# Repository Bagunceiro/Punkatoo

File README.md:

# Punkatoo

Fan and Lamp messages -> JSON
IR Reset code (c. light up)
MQTTController::publish - why is the delay needed

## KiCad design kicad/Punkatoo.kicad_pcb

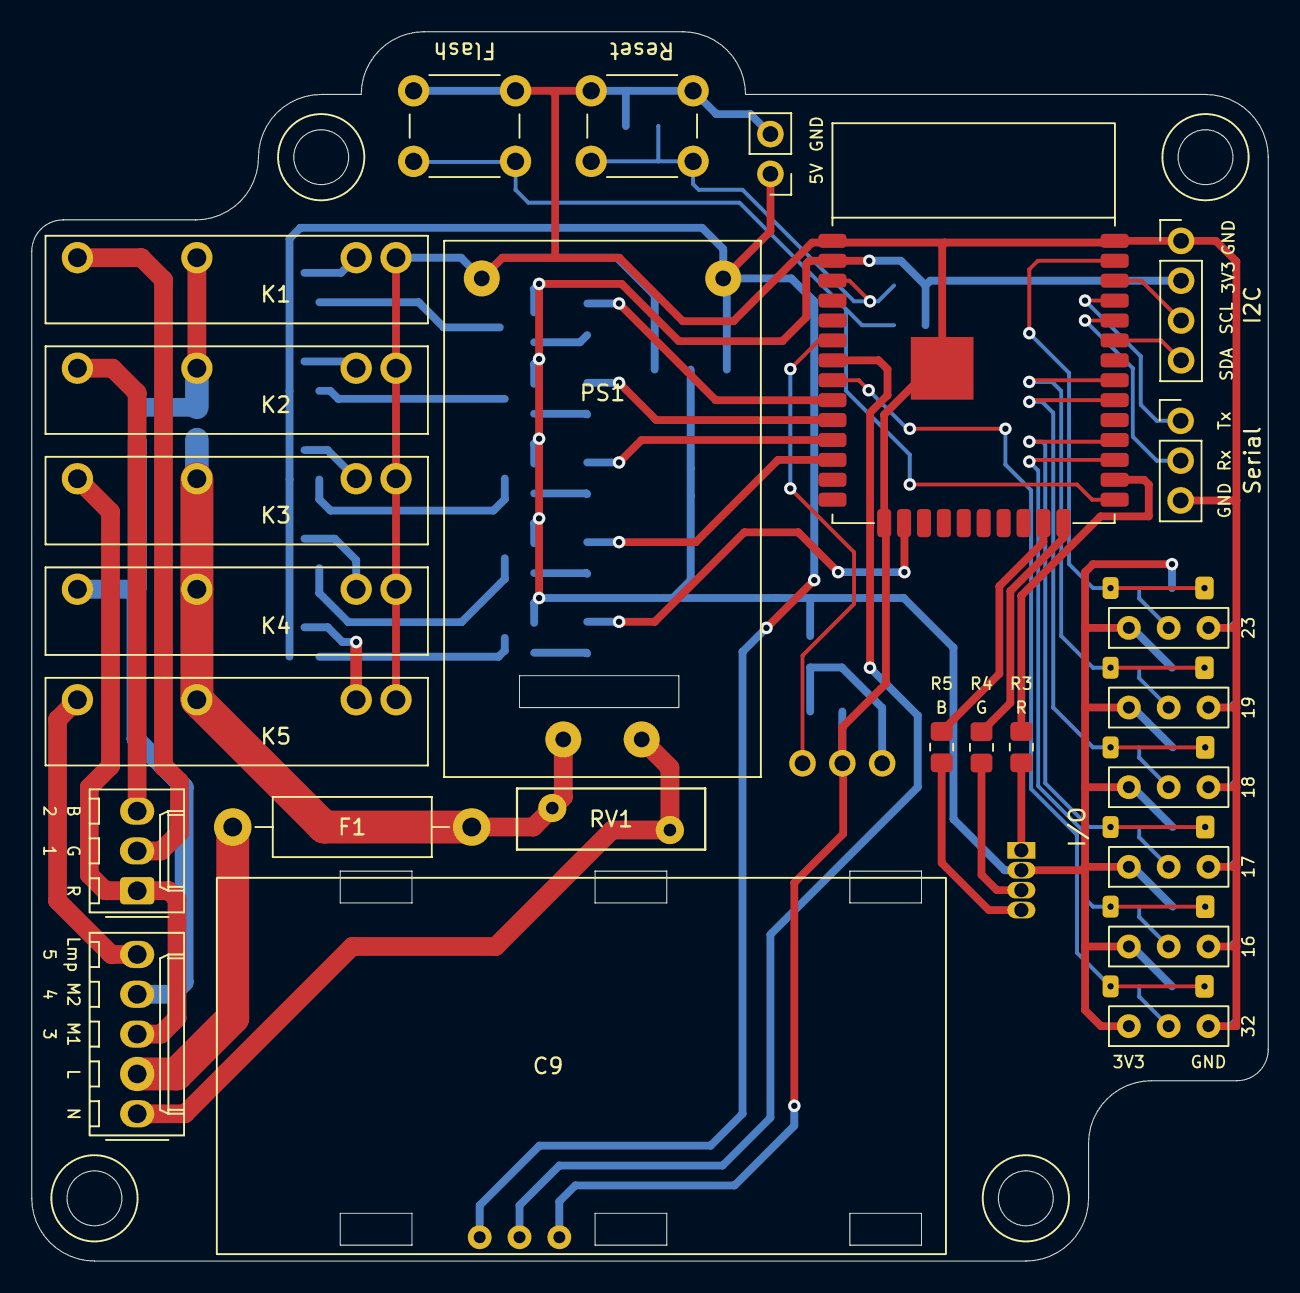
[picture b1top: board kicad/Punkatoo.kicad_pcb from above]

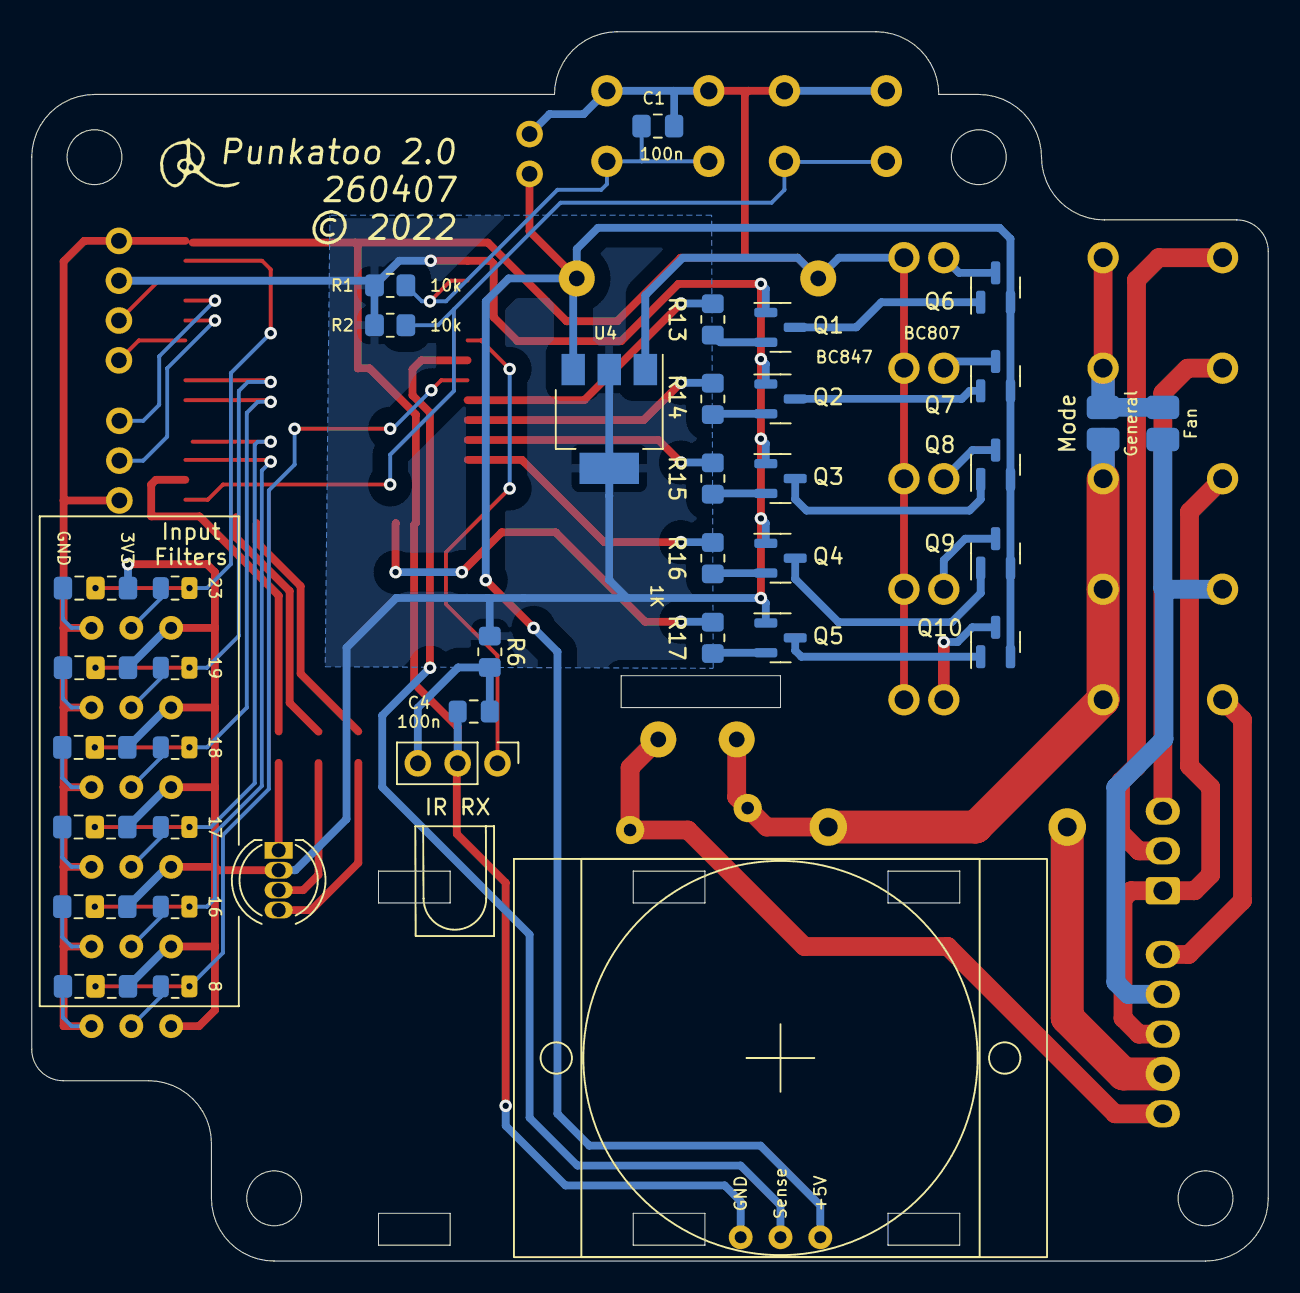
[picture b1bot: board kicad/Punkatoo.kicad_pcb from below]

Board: 2 copper layers, 78.9 x 78.4 mm, 59 parts (38 on the bottom side), 59 nets.

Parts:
C1: 100n; C_0805_2012Metric_Pad1.18x1.45mm_HandSolder
C2, C3, C5, C6, C7, C8: C_Option; C_0805_Option
C4: 100n; C_0805_2012Metric_Pad1.15x1.40mm_HandSolder
C9: Capacitor; 3Wire_2.5uF+4.5uF
D1: LED_RGBA; LED_D5.0mm-4_RGB
F1: 3A; R_Axial_DIN0411_L9.9mm_D3.6mm_P15.24mm_Horizontal
J1: 5V Power; PinHeader_1x02_P2.54mm_Vertical
J2: Serial; PinHeader_1x03_P2.54mm_Vertical
J3: I/O; Conn_03x06
J4: I2C; PinHeader_1x04_P2.54mm_Vertical
J5: Capacitor; Molex_KK-254_AE-6410-03A_1x03_P2.54mm_Vertical
J6: A/C; Molex_KK-254_AE-6410-05A_1x05_P2.54mm_Vertical
JP1: General; R_0805_2012Metric_Pad1.15x1.40mm_HandSolder
JP2: Fan; R_0805_2012Metric_Pad1.15x1.40mm_HandSolder
K1, K2, K3, K4, K5: G3MB-Relay_SolidState; G3MB
PS1: HLK-PM01; HLK-PMxx
Q1, Q2, Q3, Q4, Q5: BC847; SOT-23
Q6, Q7, Q8, Q9, Q10: BC807; SOT-23
R1, R2: 10k; R_0805_2012Metric_Pad1.20x1.40mm_HandSolder
R3: R; R_0805_2012Metric_Pad1.20x1.40mm_HandSolder
R4: G; R_0805_2012Metric_Pad1.20x1.40mm_HandSolder
R5: B; R_0805_2012Metric_Pad1.20x1.40mm_HandSolder
R6: 100; R_0805_2012Metric_Pad1.20x1.40mm_HandSolder
R7, R8, R9, R10, R11, R12: 1K; R_0805+THT
R13, R14, R15, R16, R17: 1K; R_0805_2012Metric_Pad1.20x1.40mm_HandSolder
RV1: Varistor; RV_Disc_D12mm_W3.9mm_P7.5mm
SW1: Reset; SW_PUSH_6mm_H5mm
SW2: Flash; SW_PUSH_6mm_H5mm
U1: ESP32-WROOM-32; wroom32
U2: PIR
U3: IR RX; TSOP38
U4: AMS1117-3.3; SOT-223-3_TabPin2

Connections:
+3V3: C2.1, C3.1, C5.1, C6.1, C7.1, C8.1, D1.2 (A), J3.7, J4.2, Q1.1 (B), Q2.1 (B), Q3.1 (B), Q4.1 (B), Q5.1 (B), R1.2, R2.1, R6.1, U1.2 (VDD), U4.2 (VO)
+5V: J1.1, PS1.4 (+Vout), Q6.2 (E), Q7.2 (E), Q8.2 (E), Q9.2 (E), Q10.2 (E), U2.3 (V+), U4.3 (VI)
/8: C2.2, R7.1, U1.8 (IO32)
/16: C3.2, R8.1, U1.27 (IO16)
/17: C5.2, R9.1, U1.28 (IO17)
/18: C6.2, R10.1, U1.30 (IO18)
/19: C7.2, R11.1, U1.31 (IO19)
/23: C8.2, R12.1, U1.37 (IO23)
/C_Blue: J5.3, K2.1
/C_Green: J5.2, K1.1
/C_Red: J5.1, J6.3, K3.1
/Flash: R2.2, SW2.1, U1.25 (IO0)
/IR: U1.6 (IO34), U3.1 (OUT)
/IndB: R5.1, U1.23 (IO15)
/IndG: R4.1, U1.24 (IO2)
/IndR: R3.1, U1.26 (IO4)
/LINE: F1.2, J6.2
/LMP: J6.5, K5.1
/M2: J6.4, JP2.2 (B), K4.1
/PIR: U1.7 (IO35), U2.2 (OUT)
/RXD: J2.2, U1.34 (RXD0/IO3)
/Reset: C1.2, R1.1, SW1.2, U1.3 (EN)
/TXD: J2.1, U1.35 (TXD0/IO1)
Fused: F1.1, JP1.2 (B), K3.2, K4.2, K5.2, PS1.1 (AC/L), RV1.2
GND: C1.1, C2.3, C3.3, C4.2, C5.3, C6.3, C7.3, C8.3, J1.2, J2.3, J3.8, J4.1, K1.4 (INP-), K2.4 (INP-), K3.4 (INP-), K4.4 (INP-), K5.4 (INP-), PS1.3 (-Vout), SW1.1, SW2.2, U1.1 (GND), U1.15 (GND), U1.38 (GND), U1.39 (GND), U2.1 (GND), U3.2 (GND), U4.1 (GND)
unnamed: C4.1, R6.2, U3.3 (Vs)
unnamed: D1.1 (RK), R3.2
unnamed: D1.3 (GK), R4.2
unnamed: D1.4 (BK), R5.2
unnamed: J3.1, R12.2
unnamed: J3.2, R11.2
unnamed: J3.3, R10.2
unnamed: J3.4, R9.2
unnamed: J3.5, R8.2
unnamed: J3.6, R7.2
unnamed: J4.3, U1.36 (IO22)
unnamed: J4.4, U1.33 (IO21)
unnamed: JP1.1 (A), JP2.1 (A), K1.2, K2.2
unnamed: K1.3 (INP+), Q6.3 (C)
unnamed: K2.3 (INP+), Q7.3 (C)
unnamed: K3.3 (INP+), Q8.3 (C)
unnamed: K4.3 (INP+), Q9.3 (C)
unnamed: K5.3 (INP+), Q10.3 (C)
unnamed: Q1.2 (E), R13.2
unnamed: Q1.3 (C), Q6.1 (B)
unnamed: Q2.2 (E), R14.2
unnamed: Q2.3 (C), Q7.1 (B)
unnamed: Q3.2 (E), R15.2
unnamed: Q3.3 (C), Q8.1 (B)
unnamed: Q4.2 (E), R16.2
unnamed: Q4.3 (C), Q9.1 (B)
unnamed: Q5.2 (E), R17.1
unnamed: Q5.3 (C), Q10.1 (B)
Neutral: J6.1, PS1.2 (AC/N), RV1.1
R1: R13.1, U1.9 (IO33)
R2: R14.1, U1.10 (IO25)
R3: R15.1, U1.11 (IO26)
R4: R16.1, U1.12 (IO27)
R5: R17.2, U1.16 (IO13)

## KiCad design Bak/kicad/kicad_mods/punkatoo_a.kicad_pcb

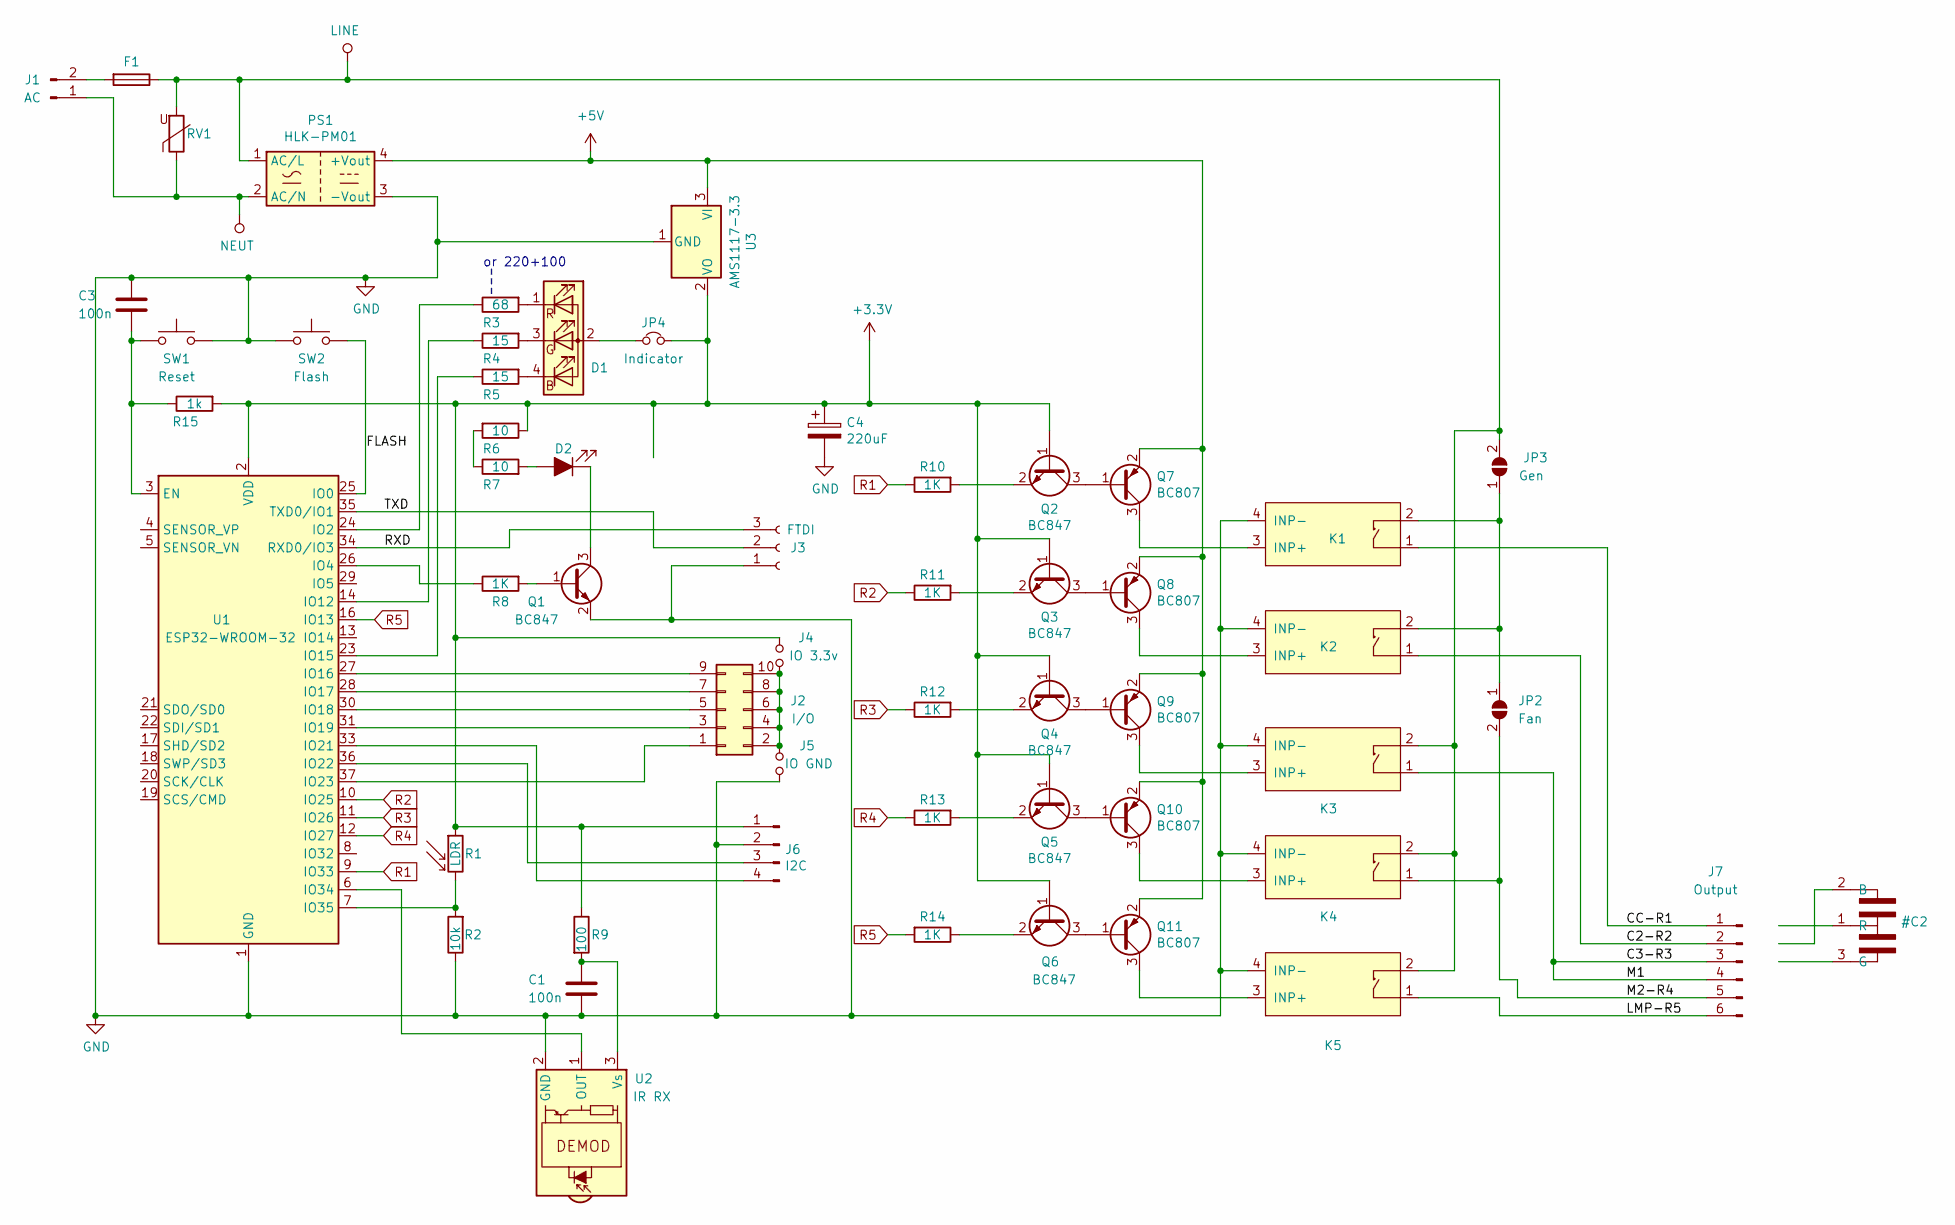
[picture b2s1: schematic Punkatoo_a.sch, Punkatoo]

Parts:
C1, C3: 100n; C_0805_2012Metric_Pad1.15x1.40mm_HandSolder
C4: 220uF; CP_Radial_D8.0mm_P2.50mm
D1: LED_RGBA; LED_D5.0mm-4_RGB
D2: IR TX; LED_D5.0mm
F1: Fuse; R_Axial_DIN0411_L9.9mm_D3.6mm_P15.24mm_Horizontal
J1: AC; Molex_KK-254_AE-6410-02A_1x02_P2.54mm_Vertical
J2: I/O; PinHeader_2x05_P2.54mm_Vertical
J3: FTDI; PinSocket_1x03_P2.54mm_Vertical
J4: IO 3.3v; R_0805_2012Metric_Pad1.15x1.40mm_HandSolder
J5: IO GND; R_0805_2012Metric_Pad1.15x1.40mm_HandSolder
J6: I2C; PinHeader_1x04_P2.54mm_Vertical
J7: Output; Molex_KK-254_AE-6410-06A_1x06_P2.54mm_Vertical
JP2: Fan; R_0805_2012Metric_Pad1.15x1.40mm_HandSolder
JP3: Gen; R_0805_2012Metric_Pad1.15x1.40mm_HandSolder
JP4: Indicator; PinHeader_1x02_P2.54mm_Vertical
K1, K2, K3, K4: G3MB
K5: G3MB-Relay_SolidState; G3MB
PS1: HLK-PM01; Converter_ACDC_HiLink_HLK-PMxx
Q1, Q2, Q3, Q4, Q5, Q6: BC847; SOT-23_HandSoldering
Q7, Q8, Q9, Q10, Q11: BC807; SOT-23_HandSoldering
R1: LDR; R_LDR_5.1x4.3mm_P3.4mm_Vertical
R2: 10k; R_0805_2012Metric_Pad1.15x1.40mm_HandSolder
R3: 68; R_0805_2012Metric_Pad1.15x1.40mm_HandSolder
R4, R5: 15; R_0805_2012Metric_Pad1.15x1.40mm_HandSolder
R6, R7: 10; R_0805_2012Metric_Pad1.15x1.40mm_HandSolder
R8, R10, R11, R12, R13, R14: 1K; R_0805_2012Metric_Pad1.15x1.40mm_HandSolder
R9: 100; R_0805_2012Metric_Pad1.15x1.40mm_HandSolder
R15: 1k; R_0805_2012Metric_Pad1.15x1.40mm_HandSolder
RV1: Varistor; varistor_10mm
SW1: Reset; SW_Tactile_Straight_KSL0Axx1LFTR
SW2: Flash; SW_Tactile_Straight_KSL0Axx1LFTR
U1: ESP32-WROOM-32
U2: IR RX; TSOP38
U3: AMS1117-3.3; SOT-223-3_TabPin2

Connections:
+3V3: C4.1, J4.1, J6.1, JP4.1, Q2.1 (B), Q3.1 (B), Q4.1 (B), Q5.1 (B), Q6.1 (B), R1.1, R6.1, R9.1, R15.2, U1.2 (VDD), U3.2 (VO)
+5V: PS1.4 (+Vout), Q7.2 (E), Q8.2 (E), Q9.2 (E), Q10.2 (E), Q11.2 (E), U3.3 (VI)
/C2-R2: J7.2, K2.1
/C3-R3: J7.3, J7.4, K3.1
/CC-R1: J7.1, K1.1
/FLASH: SW2.1, U1.25 (IO0)
/LMP-R5: J7.6, K5.1
/M2-R4: J7.5, JP2.2 (B), K4.1
/RXD: J3.3, U1.34 (RXD0/IO3)
/TXD: J3.2, U1.35 (TXD0/IO1)
GND: C1.2, C3.1, C4.2, J3.1, J5.1, J6.2, K1.4 (INP-), K2.4 (INP-), K3.4 (INP-), K4.4 (INP-), K5.4 (INP-), PS1.3 (-Vout), Q1.2 (E), R2.1, SW1.1, SW2.2, U1.1 (GND), U1.15 (GND), U1.38 (GND), U1.39 (GND), U2.2 (GND), U3.1 (GND)
LINE: F1.1, JP3.2 (B), K3.2, K4.2, K5.2, PS1.1 (AC/L), RV1.2
NEUT: J1.1, PS1.2 (AC/N), RV1.1
unnamed: C1.1, R9.2, U2.3 (Vs)
unnamed: C3.2, R15.1, SW1.2, U1.3 (EN)
unnamed: D1.1 (RK), R3.2
unnamed: D1.2 (A), JP4.2
unnamed: D1.3 (GK), R4.2
unnamed: D1.4 (BK), R5.2
unnamed: D2.1 (K), Q1.3 (C)
unnamed: D2.2 (A), R7.2
unnamed: F1.2, J1.2
unnamed: J2.1, U1.37 (IO23)
unnamed: J2.3, U1.31 (IO19)
unnamed: J2.5, U1.30 (IO18)
unnamed: J2.7, U1.28 (IO17)
unnamed: J2.9, U1.27 (IO16)
unnamed: J2.2, J2.4, J2.6, J2.8, J2.10, J4.2, J5.2
unnamed: J6.3, U1.36 (IO22)
unnamed: J6.4, U1.33 (IO21)
unnamed: JP2.1 (A), JP3.1 (A), K1.2, K2.2
unnamed: K1.3 (INP+), Q7.3 (C)
unnamed: K2.3 (INP+), Q8.3 (C)
unnamed: K3.3 (INP+), Q9.3 (C)
unnamed: K4.3 (INP+), Q10.3 (C)
unnamed: K5.3 (INP+), Q11.3 (C)
unnamed: Q1.1 (B), R8.2
unnamed: Q2.2 (E), R10.2
unnamed: Q2.3 (C), Q7.1 (B)
unnamed: Q3.2 (E), R11.2
unnamed: Q3.3 (C), Q8.1 (B)
unnamed: Q4.2 (E), R12.2
unnamed: Q4.3 (C), Q9.1 (B)
unnamed: Q5.2 (E), R13.2
unnamed: Q6.2 (E), R14.1
unnamed: Q5.3 (C), Q10.1 (B)
unnamed: Q6.3 (C), Q11.1 (B)
unnamed: R1.2, R2.2, U1.7 (IO35)
unnamed: R3.1, U1.24 (IO2)
unnamed: R4.1, U1.14 (IO12)
unnamed: R5.1, U1.23 (IO15)
unnamed: R6.2, R7.1
unnamed: R8.1, U1.26 (IO4)
unnamed: U1.6 (IO34), U2.1 (OUT)
R1: R10.1, U1.9 (IO33)
R2: R11.1, U1.10 (IO25)
R3: R12.1, U1.11 (IO26)
R4: R13.1, U1.12 (IO27)
R5: R14.2, U1.16 (IO13)

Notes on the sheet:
or 220+100

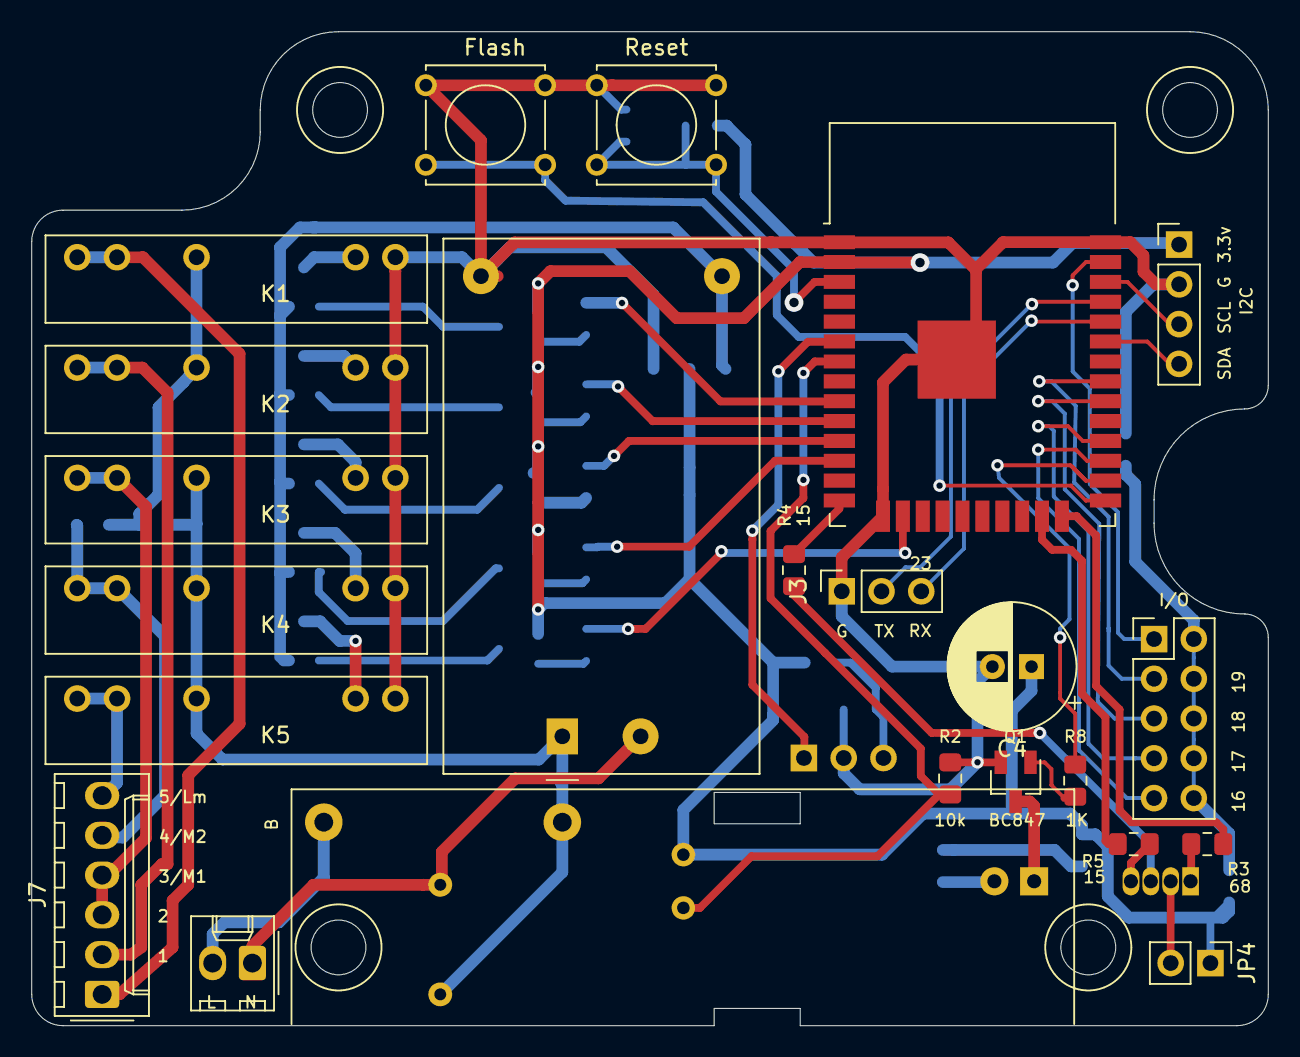
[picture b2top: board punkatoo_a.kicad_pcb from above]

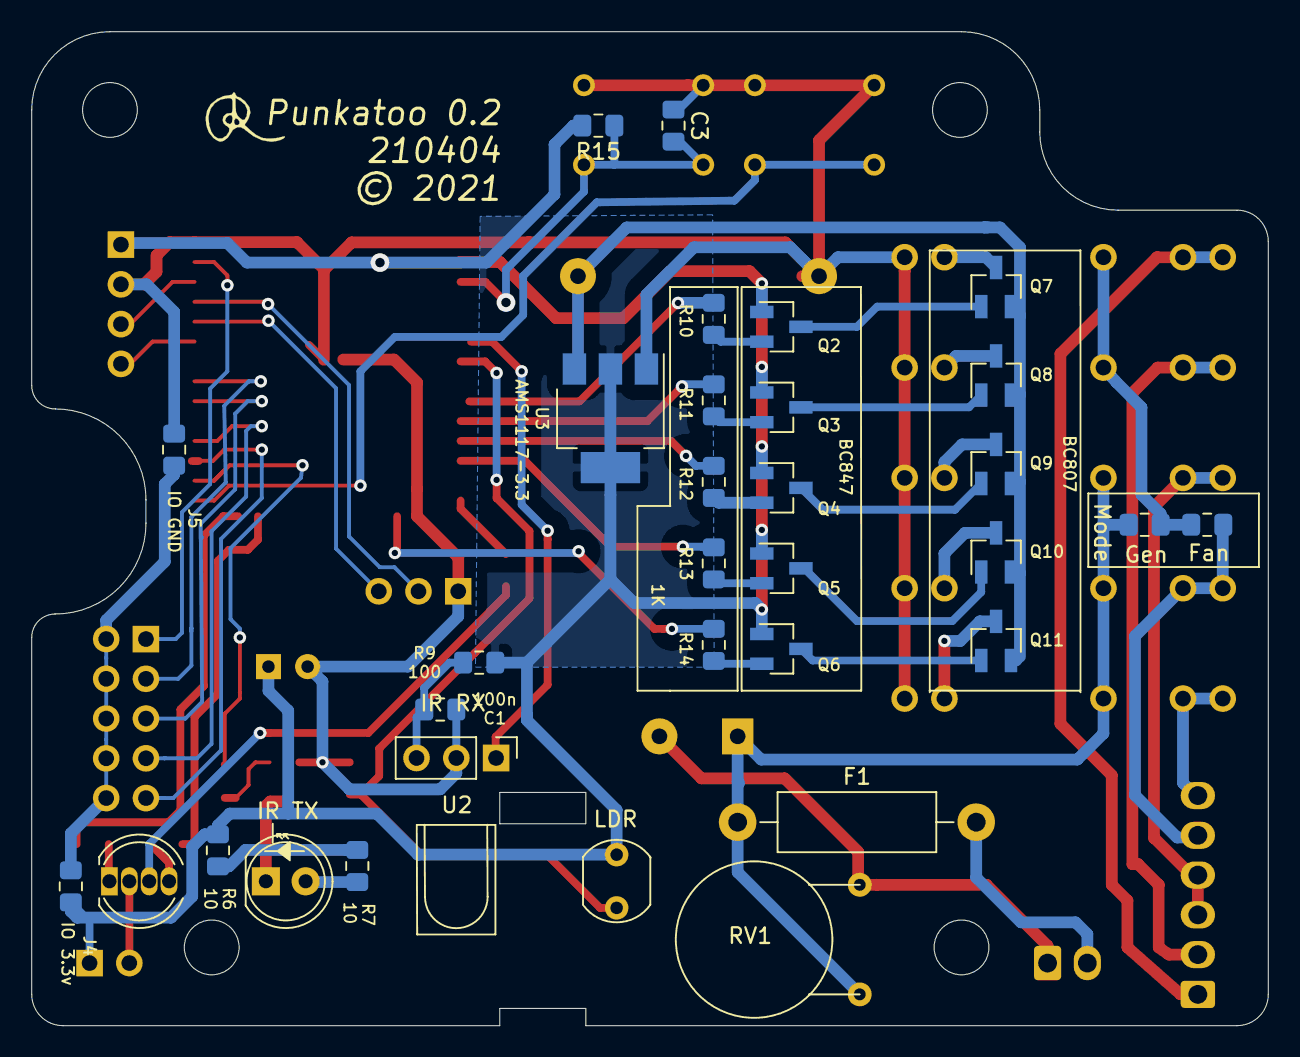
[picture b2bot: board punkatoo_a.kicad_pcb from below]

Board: 2 copper layers, 79.0 x 63.5 mm, 55 parts (32 on the bottom side), 59 nets.

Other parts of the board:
Capacitor: Ceiling_Fan_Capacitor

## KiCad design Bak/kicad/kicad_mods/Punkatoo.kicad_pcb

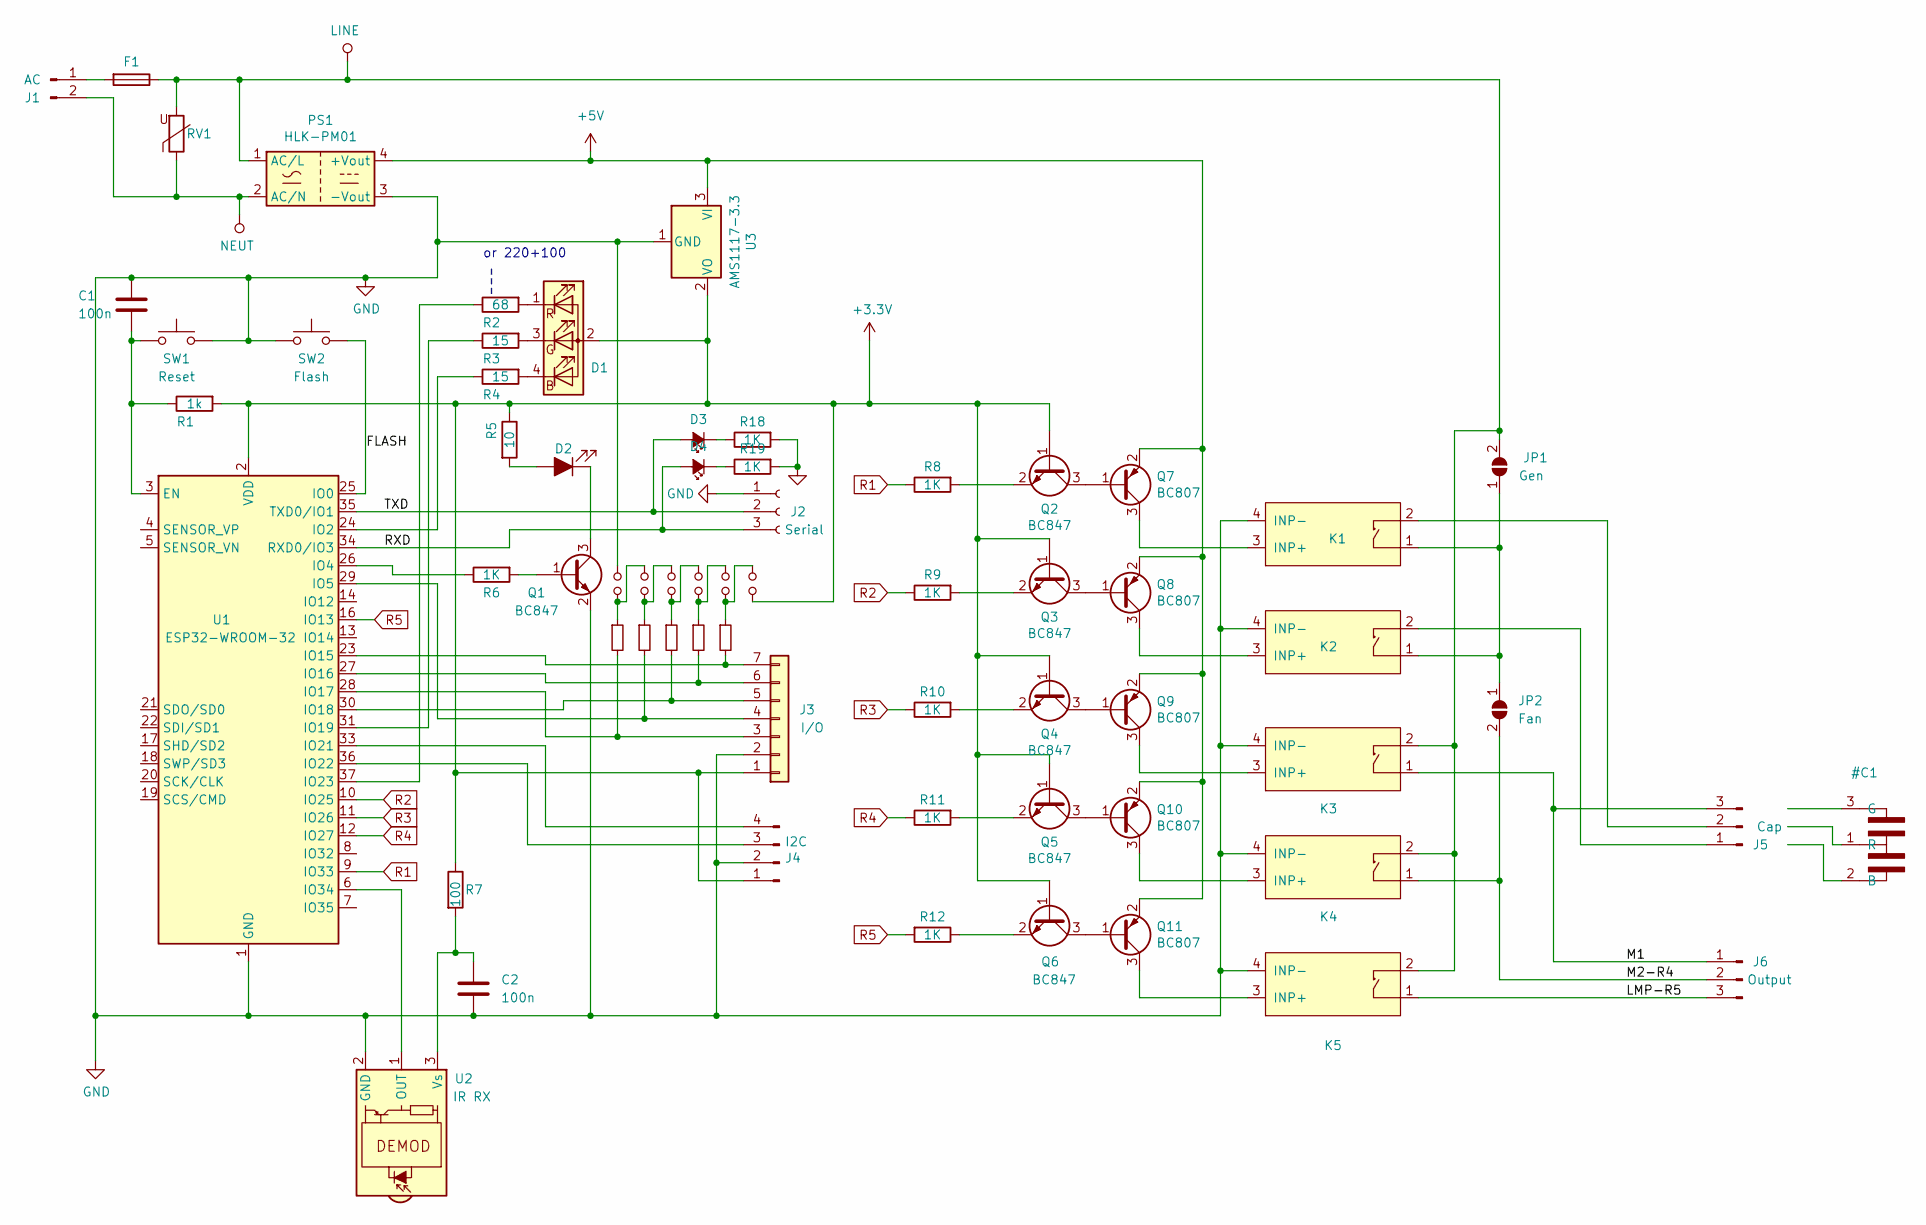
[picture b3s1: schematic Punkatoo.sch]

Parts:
C1, C2: 100n; C_0805_2012Metric_Pad1.15x1.40mm_HandSolder
D1: RGB; LED_D5.0mm-4_RGB
D2: IR TX; LED_D5.0mm
D3, D4: LED_Small_ALT; LED_0805_2012Metric_Pad1.15x1.40mm_HandSolder
F1: Fuse; R_Axial_DIN0411_L9.9mm_D3.6mm_P15.24mm_Horizontal
J1: AC; Molex_KK-254_AE-6410-02A_1x02_P2.54mm_Vertical
J2: Serial; PinHeader_1x03_P2.54mm_Vertical
J3: I/O; GPIO_5+rails_P2.54mm_Vertical
J4: I2C; PinHeader_1x04_P2.54mm_Vertical
J5: Cap; Molex_KK-254_AE-6410-03A_1x03_P2.54mm_Vertical
J6: Output; Molex_KK-254_AE-6410-03A_1x03_P2.54mm_Vertical
JP1: Gen; R_0805_2012Metric_Pad1.15x1.40mm_HandSolder
JP2: Fan; R_0805_2012Metric_Pad1.15x1.40mm_HandSolder
JP3: GND; Small_solder_jumper
JP4, JP5, JP6, JP7: Jumper_NO_Small; Small_solder_jumper
JP8: 3.3V; Small_solder_jumper
K1, K2, K3, K4: G3MB
K5: G3MB-Relay_SolidState; G3MB
PS1: HLK-PM01; Converter_ACDC_HiLink_HLK-PMxx
Q1, Q2, Q3, Q4, Q5, Q6: BC847; SOT-23_HandSoldering
Q7, Q8, Q9, Q10, Q11: BC807; SOT-23_HandSoldering
R1: 1k; R_0805_2012Metric_Pad1.15x1.40mm_HandSolder
R2: 68; R_0805_2012Metric_Pad1.15x1.40mm_HandSolder
R3, R4, R13: 15; R_0805_2012Metric_Pad1.15x1.40mm_HandSolder
R5: 10; R_0805_2012Metric_Pad1.15x1.40mm_HandSolder
R6, R8, R9, R10, R11, R12, R18, R19: 1K; R_0805_2012Metric_Pad1.15x1.40mm_HandSolder
R7: 100; R_0805_2012Metric_Pad1.15x1.40mm_HandSolder
R14: 16; R_0805_2012Metric_Pad1.15x1.40mm_HandSolder
R15: 18; R_0805_2012Metric_Pad1.15x1.40mm_HandSolder
R16: 5; R_0805_2012Metric_Pad1.15x1.40mm_HandSolder
R17: 17; R_0805_2012Metric_Pad1.15x1.40mm_HandSolder
RV1: Varistor; varistor_10mm
SW1: Reset; SW_Tactile_Straight_KSL0Axx1LFTR
SW2: Flash; SW_Tactile_Straight_KSL0Axx1LFTR
U1: ESP32-WROOM-32
U2: IR RX; TSOP38
U3: AMS1117-3.3; SOT-223-3_TabPin2

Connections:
+3V3: D1.2 (A), J3.1, J4.1, JP8.2, Q2.1 (B), Q3.1 (B), Q4.1 (B), Q5.1 (B), Q6.1 (B), R1.2, R5.1, R7.1, U1.2 (VDD), U3.2 (VO)
+5V: PS1.4 (+Vout), Q7.2 (E), Q8.2 (E), Q9.2 (E), Q10.2 (E), Q11.2 (E), U3.3 (VI)
/FLASH: SW2.1, U1.25 (IO0)
/LMP-R5: J6.3, K5.1
/M1: J5.3, J6.1, K3.1
/M2-R4: J6.2, JP2.2 (B), K4.1
/RXD: D4.2 (A), J2.3, U1.34 (RXD0/IO3)
/TXD: D3.2 (A), J2.2, U1.35 (TXD0/IO1)
GND: C1.1, C2.2, J2.1, J3.2, J4.2, JP3.1, K1.4 (INP-), K2.4 (INP-), K3.4 (INP-), K4.4 (INP-), K5.4 (INP-), PS1.3 (-Vout), Q1.2 (E), R18.2, R19.2, SW1.1, SW2.2, U1.1 (GND), U1.15 (GND), U1.38 (GND), U1.39 (GND), U2.2 (GND), U3.1 (GND); also elsewhere on the board
LINE: F1.1, JP1.2 (B), K3.2, K4.2, K5.2, PS1.1 (AC/L), RV1.2
NEUT: J1.2, PS1.2 (AC/N), RV1.1
unnamed: C1.2, R1.1, SW1.2, U1.3 (EN)
unnamed: C2.1, R7.2, U2.3 (Vs)
unnamed: D1.1 (RK), R2.2
unnamed: D1.3 (GK), R3.2
unnamed: D1.4 (BK), R4.2
unnamed: D2.1 (K), Q1.3 (C)
unnamed: D2.2 (A), R5.2
unnamed: D3.1 (K), R18.1
unnamed: D4.1 (K), R19.1
unnamed: F1.2, J1.1
unnamed: J3.3, R17.2, U1.28 (IO17)
unnamed: J3.4, R16.2, U1.29 (IO5)
unnamed: J3.5, R15.2, U1.30 (IO18)
unnamed: J3.6, R14.2, U1.27 (IO16)
unnamed: J3.7, R13.2, U1.23 (IO15)
unnamed: J4.3, U1.36 (IO22)
unnamed: J4.4, U1.33 (IO21)
unnamed: J5.1, K2.2
unnamed: J5.2, K1.2
unnamed: JP1.1 (A), JP2.1 (A), K1.1, K2.1
unnamed: JP3.2, JP4.1, R17.1
unnamed: JP4.2, JP5.1, R16.1
unnamed: JP5.2, JP6.1, R15.1
unnamed: JP6.2, JP7.1, R14.1
unnamed: JP7.2, JP8.1, R13.1
unnamed: K1.3 (INP+), Q7.3 (C)
unnamed: K2.3 (INP+), Q8.3 (C)
unnamed: K3.3 (INP+), Q9.3 (C)
unnamed: K4.3 (INP+), Q10.3 (C)
unnamed: K5.3 (INP+), Q11.3 (C)
unnamed: Q1.1 (B), R6.2
unnamed: Q2.2 (E), R8.2
unnamed: Q2.3 (C), Q7.1 (B)
unnamed: Q3.2 (E), R9.2
unnamed: Q3.3 (C), Q8.1 (B)
unnamed: Q4.2 (E), R10.2
unnamed: Q4.3 (C), Q9.1 (B)
unnamed: Q5.2 (E), R11.2
unnamed: Q6.2 (E), R12.1
unnamed: Q5.3 (C), Q10.1 (B)
unnamed: Q6.3 (C), Q11.1 (B)
unnamed: R2.1, U1.37 (IO23)
unnamed: R3.1, U1.31 (IO19)
unnamed: R4.1, U1.24 (IO2)
unnamed: R6.1, U1.26 (IO4)
unnamed: U1.6 (IO34), U2.1 (OUT)
R1: R8.1, U1.9 (IO33)
R2: R9.1, U1.10 (IO25)
R3: R10.1, U1.11 (IO26)
R4: R11.1, U1.12 (IO27)
R5: R12.2, U1.16 (IO13)

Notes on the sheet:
or 220+100

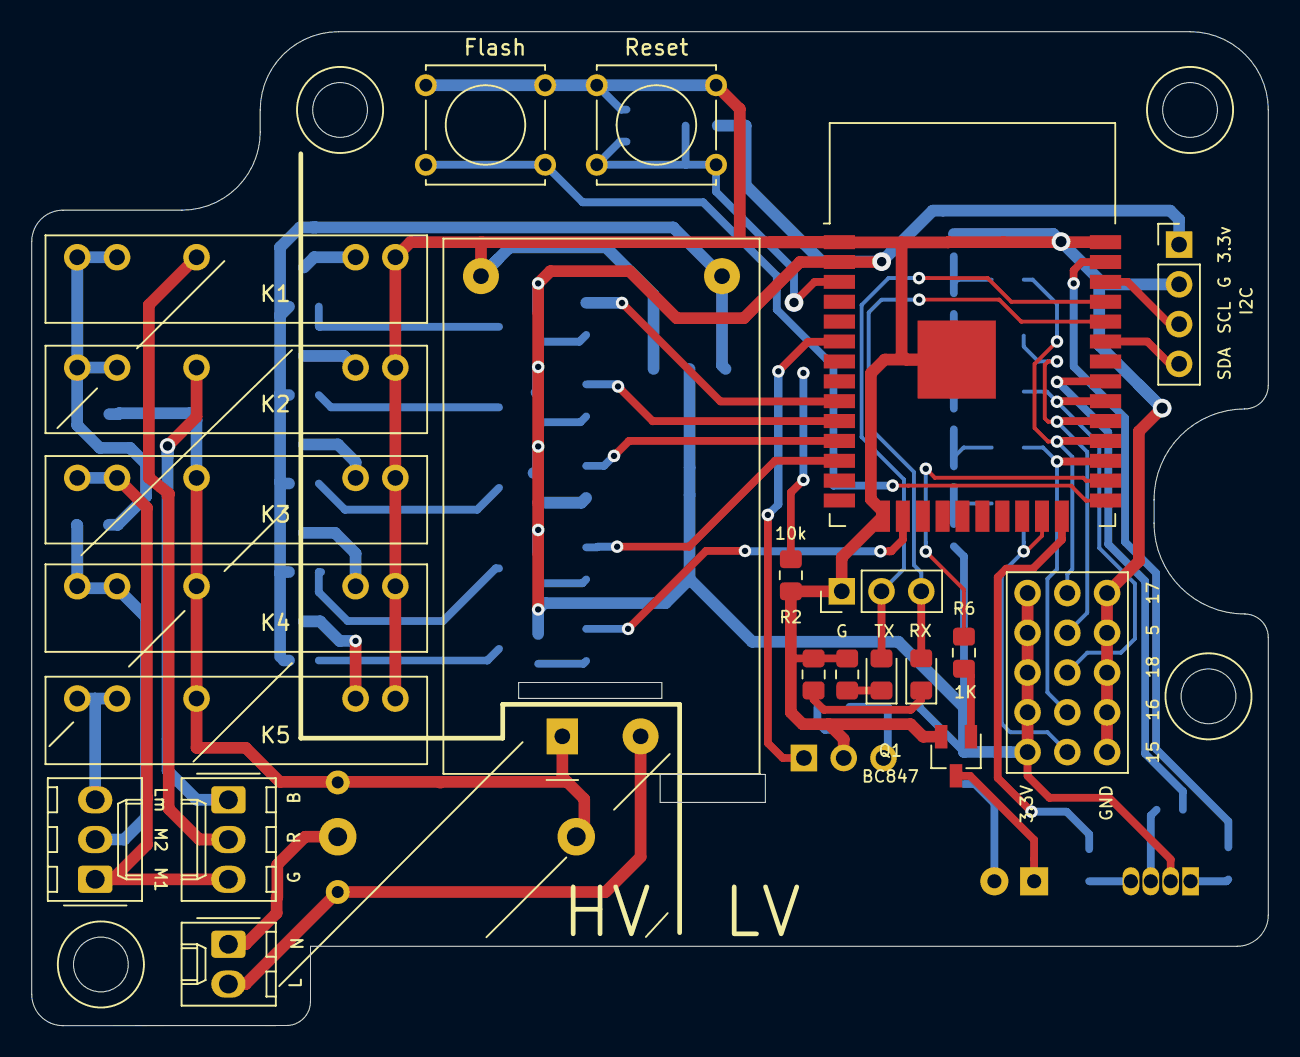
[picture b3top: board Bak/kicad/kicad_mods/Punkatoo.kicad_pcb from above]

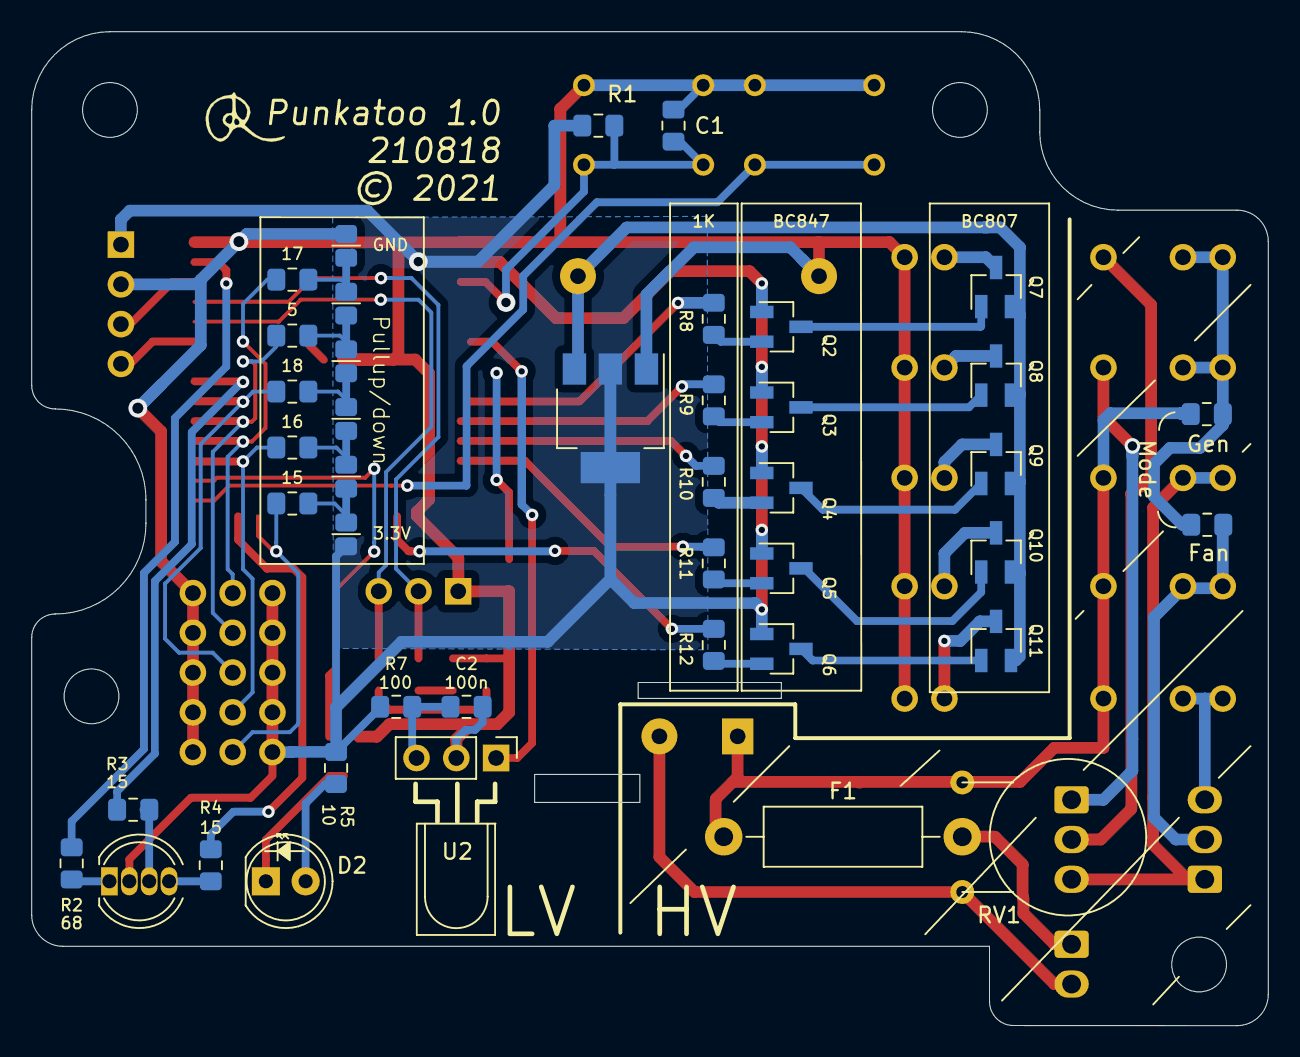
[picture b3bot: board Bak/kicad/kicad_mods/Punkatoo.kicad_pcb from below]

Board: 2 copper layers, 79.0 x 63.5 mm, 64 parts (42 on the bottom side), 62 nets.

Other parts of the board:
R2#2: 10k; R_0805_2012Metric_Pad1.15x1.40mm_HandSolder

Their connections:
GND: R2#2.1; also elsewhere on the board

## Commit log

2021-01-22 ESP32 version
2021-01-31 Corrections for fan after test
2021-01-31 Correct ordering of speed relays
2021-01-31 Removing conditional compilations and left over commentings out
2021-01-31 more cond comp
2021-02-02 Tidyings Protect against missing temp sensor Timestamp to ISO-8601
2021-02-06 New IR Polling mech
2021-02-06 Enable IR sub mech
2021-02-06 enable seperate lamp and IR tasks
2021-02-06 PTask (ircontroller)
2021-02-06 Tidyup
2021-02-07 Restore working - stack sizes
2021-02-07 Improved WiFi reconnection
2021-02-07 Correct IR decode table
2021-02-09 Before working on WSerial
2021-02-09 WSerial simplified and IR Messages reported
2021-02-09 EventLog
2021-02-10 incorporate external libs
2021-02-10 V0.2
2021-02-10 Event serial numbers
2021-02-11 Log to Webserver
2021-02-11 MQTT subscribe mech
2021-02-11 MQTT mech
2021-02-11 Instantiate Updater only when needed
2021-02-12 event log tweeks
2021-02-16 Add event log
2021-02-17 210217
2021-02-25 Clear out rubbish
2021-02-25 States
2021-02-25 remove old commented out lines
2021-02-25 Interval constants
2021-02-26 Improved indicator colours
2021-02-26 reset from IR
2021-02-27 Simplify WPS
2021-03-01 Various corrections - IR output enabled
2021-03-01 JSON Message for MQTT Send IR code
2021-03-02 Objectising
2021-03-02 tidy
2021-03-03 Fan to Devices
2021-03-03 Lamp to devices
2021-03-03 LDR to devices
2021-03-03 P2State class
2021-03-04 device configuration + active switches
2021-03-08 tidy old commentings out
2021-03-11 ignore the kicad file
2021-03-11 ad kicad files
2021-03-11 kicad files
2021-03-11 Remove unwanted kicad files
2021-03-11 remove inappropriate enviroments (and other junk)
2021-03-22 Handling of unknown IR messages
2021-03-22 Improve naming and commentary
2021-03-22 Known issues
2021-03-22 Shift WiFi Serial onto port 1685
2021-03-23 minor
2021-03-23 P2System created. P2State subsumed into it. Configurator withdrawn.
2021-03-23 Fully remove configurator and p2state. Disable SPDT state 3 (both relays energised).
2021-03-24 Improved Logging timestamps
2021-03-24 Removal of commented-out code
2021-03-24 After messed up merge
2021-03-25 Comments
2021-03-25 Device Config File
2021-03-25 Tidying
2021-03-25 Automation of build version
2021-03-25 Up version number
2021-03-25 Build process
2021-03-25 Version reporting
2021-03-25 Remove no longer required OTA time and hard GPIO pin definitions
2021-04-01 add const for niceness
2021-04-08 Correct timestamp
2021-04-25 Fan problem correction (needs position 3 for full speed)
2021-04-25 Implement async web server
2021-04-25 Add dynamic fields
2021-04-26 system update non-blocking Async events to web server
2021-04-26 system update pages
2021-04-26 lose junk swap file
2021-04-26 correct pressure display
2021-04-26 stylesheet and js files
2021-04-27 reset offloaded to p2system
2021-04-27 Update::CBs to WS
2021-04-28 Web server improvements JSON heartbeat info
2021-04-28 various
2021-04-28 regex for served files
2021-04-28 remove regex server!
2021-04-28 Use onNotFound for serving files
2021-04-29 Initial seperated HTML works
2021-04-29 network list nearly works (!)
2021-04-30 Nearer still
2021-04-30 netedit works
2021-04-30 sysupd works
2021-04-30 HTML separation complete
2021-05-01 Add CLITask (only echos input as yet)
2021-05-01 file upload via "upload SERVER PORT SOURCE TARGET" on port 1685
2021-05-02 web fixes sysupdate over cli
2021-05-02 Web page update withdrawn
2021-05-03 V10.1 released
2021-05-03 tidying up
2021-05-09 Corrections to networks list
2021-05-20 Report WiFi RSSI and BSSID
2021-05-20 Size of JSON doc for network list
2021-05-30 Serial monitor to 115600
2021-06-07 virtual switches working
2021-06-08 Enhanced CLI
2021-06-09 added cli utils
2021-06-13 heartbeat
2021-06-15 watchdog changes
2021-06-24 devices
2021-06-25 Correct devices file for IR code
2021-06-25 Prevent clobbering of PSK
2021-07-05 Not sure
2021-07-08 Corrected networks definition file (psk was missing)
2021-08-20 Swap Lamp switchto and switch topics
2021-10-07 Fix device configuration for office
2021-12-19 Climate measurement presentation
2022-02-26 visual feedback for fan switching
2022-04-11 physical switching
2022-04-11 Device Corrections
2022-04-25 Mods for update of ESP32 framework to 4.1.0
2022-04-26 V2.0 PCB prepared for manufacture
2022-04-26 Mini correction to PCB
2022-05-01 Ignore backup directory
2022-05-22 data dir structure
2022-05-23 Added PIR
2022-05-23 Remove debug
2022-05-24 Restructure (simplify to flat) file system.
2022-05-26 encrypt psks in networks file
2022-05-27 encrypt configuration
2022-05-27 Hide MQTT password
2022-05-30 seperate config
2022-06-07 literals -> constants
2022-06-09 Use bme address from config
2022-06-10 weather station
2022-06-11 Move switch list to switches task
2022-06-11 fsupdate
2022-06-11 irctlr as object rather than pointer
2022-06-16 Tidy Project Structure
2022-08-13 fix PIR
2022-08-24 Switches stack overflow
2022-08-25 Adding doxygen tags
2022-08-25 doxygen tags
2022-08-25 Remove weather station code
2022-08-25 Remove LDR code
2022-08-25 Unpick P2Sys - move status indication functionality to indicator
2022-08-26 sort out doSwitch oddness
2022-08-26 Unnecessary Strings in interfaces
2022-08-26 Unpick WiFi Serial
2022-08-26 Simplifying includes
2022-08-27 Commentary - various tidyings
2023-04-03 Remove compiler define -D CONFIG_LITTLEFS_FOR_IDF_3_2 (no longer required)

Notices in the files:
Bak/kicad/kicad_mods/Punkatoo.kicad_pcb:
© 2021
kicad/Punkatoo.kicad_pcb:
© 2022
